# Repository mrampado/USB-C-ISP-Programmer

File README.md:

# USB-C-ISP-Programmer
ISP programmer for ATMEGA based Arduino boards with a USB C header, a more compact form, and easy to use design

Current status as of latest commit to master:
- Initial hardware complete, creating order to JLC
- More documentation to follow as hardware is received and brought up

### Bonus
A little bonus for those that reconize it

## License

This hardware is covered under the CERN-OHL-S-V2 open source hardware license. Details on this license can also be found [at this link](https://choosealicense.com/licenses/cern-ohl-s-2.0/). 

Software for this project is covered under GNU Public License v3.0. Details on this license can be found [at this link](https://choosealicense.com/licenses/gpl-3.0/)

As per the details in each of the licenses, replication is accepted under the provision that all commercial and individual replications must also follow the same license as in this project, and **remain fully open source**. 

While not required, please contact me before starting any commercialization efforts. At the current moment, I am unable to commercialize this project thus unable to sell finished boards. I am happy to (in a limited capacity) support anyone / business that wants to utilize my efforts with ALP to use as a basis for teaching anyone and everyone Arduino. 

It is my personal belief that this project shall remain open source for the entire community, with all schematics, gerber files, and code available to all. I have benefited greatly from the open source community and this project will hopefully help others learn and get started too!

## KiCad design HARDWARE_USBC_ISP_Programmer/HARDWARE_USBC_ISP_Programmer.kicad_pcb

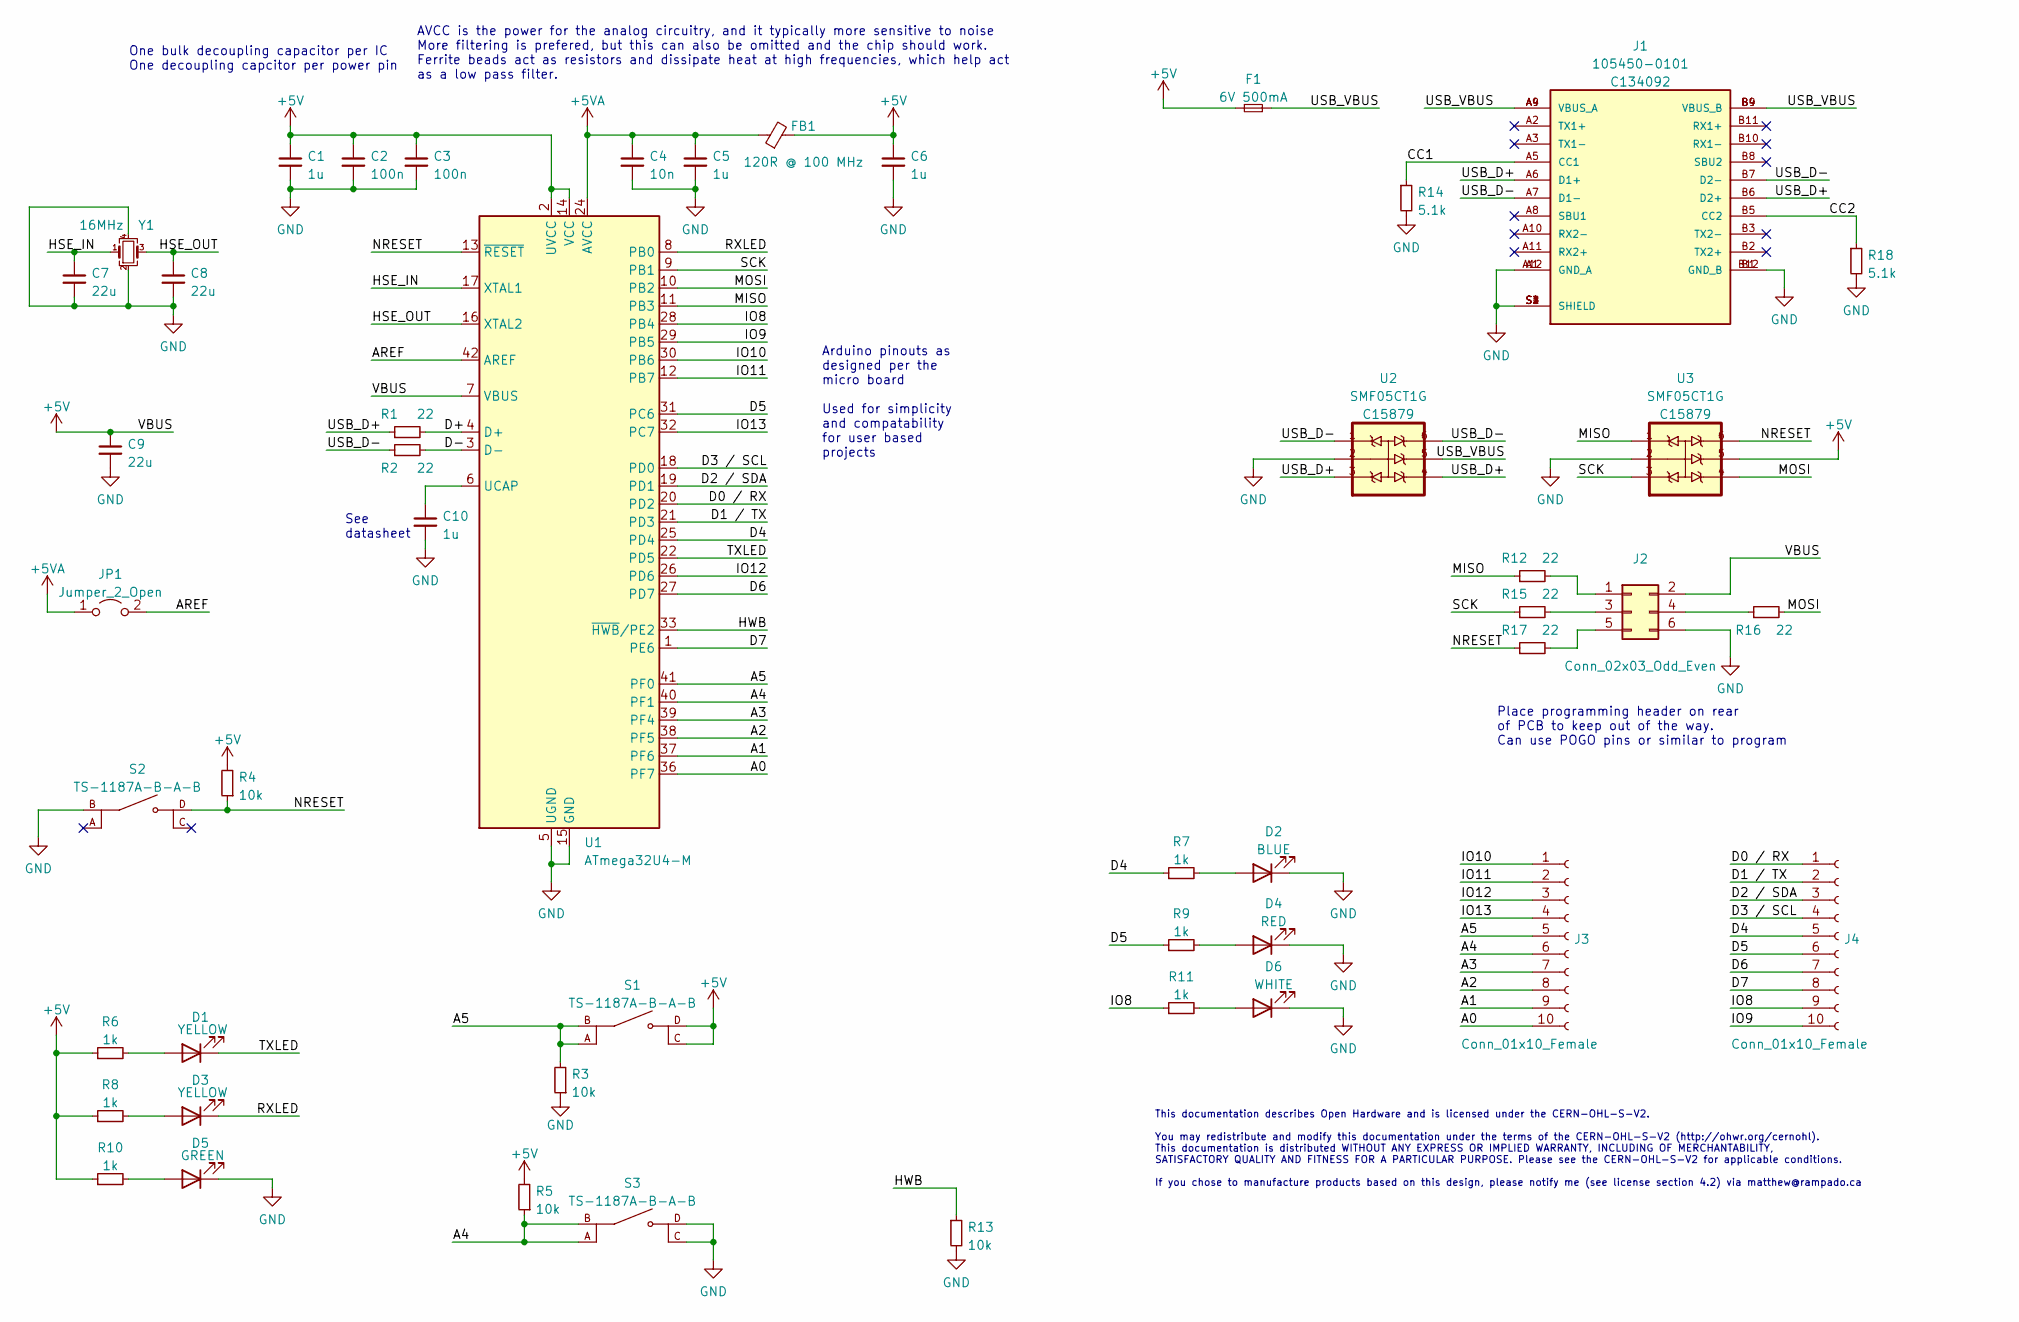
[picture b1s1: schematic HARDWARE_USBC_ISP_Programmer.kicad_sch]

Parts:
C1, C5, C6, C10: 1u; C_0603_1608Metric; JLCPCB Part # C15849
C2, C3: 100n; C_0603_1608Metric; JLCPCB Part # C14663
C4: 10n; C_0603_1608Metric; JLCPCB Part # C57112
C7, C8, C9: 22u; C_0603_1608Metric; JLCPCB Part # C59461
D1, D3: YELLOW; LED_0603_1608Metric; JLCPCB Part # C72038
D2: BLUE; LED_0603_1608Metric; JLCPCB Part # C72041
D4: RED; LED_0603_1608Metric; JLCPCB Part # C2286
D5: GREEN; LED_0603_1608Metric; JLCPCB Part # C72043
D6: WHITE; LED_0603_1608Metric; JLCPCB Part # C2290
F1: 6V 500mA; Fuse_0603_1608Metric_Pad1.05x0.95mm_HandSolder; JLCPCB Part # C135323
FB1: 120R @ 100 MHz; L_0805_2012Metric; JLCPCB Part # C1015
J1: 105450-0101; MOLEX_105450-0101; PARTREV A7; JLCPCB Part # C134092
J2: Conn_02x03_Odd_Even; PinHeader_2x03_P2.54mm_Vertical; JLCPCB Part # C65114
J3, J4: Conn_01x10_Female; PinSocket_1x10_P2.54mm_Vertical
JP1: Jumper_2_Open; SolderJumper-2_P1.3mm_Open_RoundedPad1.0x1.5mm; JLCPCB Part # N/A
R1, R2, R12, R15, R16, R17: 22; R_0603_1608Metric; JLCPCB Part # C23345
R3, R4, R5, R13: 10k; R_0603_1608Metric; JLCPCB Part # C25804
R6, R7, R8, R9, R10, R11: 1k; R_0603_1608Metric; JLCPCB Part # C21190
R14, R18: 5.1k; R_0603_1608Metric; JLCPCB Part # C23186
S1, S2, S3: TS-1187A-B-A-B; SW_TS-1187A-B-A-B; PARTREV A0; JLCPCB Part # C318884
U1: ATmega32U4-M; QFN-44-1EP_7x7mm_P0.5mm_EP5.2x5.2mm; JLCPCB Part # C112161
U2, U3: SMF05CT1G; SOT65P210X110-6N; JLCPCB Part # C15879
Y1: 16MHz; Crystal_SMD_3225-4Pin_3.2x2.5mm; JLCPCB Part # C112972

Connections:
+5V: C1.1, C2.1, C3.1, C6.1, C9.1, F1.1, FB1.2, J2.2, R4.2, R5.2, R6.1, R8.1, R10.1, S1.C, S1.D, U1.2 (UVCC), U1.7 (VBUS), U1.14 (VCC), U1.34 (VCC), U3.5
+5VA: C4.1, C5.1, FB1.1, JP1.1 (A), U1.24 (AVCC), U1.44 (AVCC)
/A0: J3.10, U1.36 (PF7)
/A1: J3.9, U1.37 (PF6)
/A2: J3.8, U1.38 (PF5)
/A3: J3.7, U1.39 (PF4)
/A4: J3.6, R5.1, S3.A, S3.B, U1.40 (PF1)
/A5: J3.5, R3.2, S1.A, S1.B, U1.41 (PF0)
/AREF: JP1.2 (B), U1.42 (AREF)
/CC1: J1.A5 (CC1), R14.1
/CC2: J1.B5 (CC2), R18.1
/D0 / RX: J4.1, U1.20 (PD2)
/D1 / TX: J4.2, U1.21 (PD3)
/D2 / SDA: J4.3, U1.19 (PD1)
/D3 / SCL: J4.4, U1.18 (PD0)
/D4: J4.5, R7.1, U1.25 (PD4)
/D5: J4.6, R9.1, U1.31 (PC6)
/D6: J4.7, U1.27 (PD7)
/D7: J4.8, U1.1 (PE6)
/D+: R1.2, U1.4 (D+)
/D-: R2.2, U1.3 (D-)
/HSE_IN: C7.1, U1.17 (XTAL1), Y1.1
/HSE_OUT: C8.1, U1.16 (XTAL2), Y1.3
/HWB: R13.1, U1.33 (~HWB/PE2)
/IO8: J4.9, R11.1, U1.28 (PB4)
/IO9: J4.10, U1.29 (PB5)
/IO10: J3.1, U1.30 (PB6)
/IO11: J3.2, U1.12 (PB7)
/IO12: J3.3, U1.26 (PD6)
/IO13: J3.4, U1.32 (PC7)
/MISO: R12.1, U1.11 (PB3), U3.1
/MOSI: R16.2, U1.10 (PB2), U3.4
/NRESET: R4.1, R17.1, S2.D, U1.13 (~RESET), U3.6
/RXLED: D3.1 (K), U1.8 (PB0)
/SCK: R15.1, U1.9 (PB1), U3.3
/TXLED: D1.1 (K), U1.22 (PD5)
/USB_D+: J1.A6 (D1+), J1.B6 (D2+), R1.1, U2.3, U2.4
/USB_D-: J1.A7 (D1-), J1.B7 (D2-), R2.1, U2.1, U2.6
/USB_VBUS: F1.2, J1.A4 (VBUS_A), J1.A9 (VBUS_A), J1.B4 (VBUS_B), J1.B9 (VBUS_B), U2.5
GND: C1.2, C2.2, C3.2, C4.2, C5.2, C6.2, C7.2, C8.2, C9.2, C10.2, D2.1 (K), D4.1 (K), D5.1 (K), D6.1 (K), J1.A1 (GND_A), J1.A12 (GND_A), J1.B1 (GND_B), J1.B12 (GND_B), J1.S1 (SHIELD), J1.S2 (SHIELD), J1.S3 (SHIELD), J1.S4 (SHIELD), J2.6, R3.1, R13.2, R14.2, R18.2, S2.B, S3.C, S3.D, U1.5 (UGND), U1.15 (GND), U1.23 (GND), U1.35 (GND), U1.43 (GND), U1.45 (GND), U2.2, U3.2, Y1.2, Y1.4
unnamed: C10.1, U1.6 (UCAP)
unnamed: D1.2 (A), R6.2
unnamed: D2.2 (A), R7.2
unnamed: D3.2 (A), R8.2
unnamed: D4.2 (A), R9.2
unnamed: D5.2 (A), R10.2
unnamed: D6.2 (A), R11.2
unnamed: J2.1, R12.2
unnamed: J2.3, R15.2
unnamed: J2.4, R16.1
unnamed: J2.5, R17.2

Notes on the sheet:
Place programming header on rear of PCB to keep out of the way. Can use POGO pins or similar to program
AVCC is the power for the analog circuitry, and it typically more sensitive to noise More filtering is prefered, but this can also be omitted and the chip should work. Ferrite beads act as resistors and dissipate heat at high frequencies, which help act as a low pass filter.
See datasheet
One bulk decoupling capacitor per IC One decoupling capcitor per power pin
This documentation describes Open Hardware and is licensed under the CERN-OHL-S-V2. You may redistribute and modify this documentation under the terms of the CERN-OHL-S-V2 (http://ohwr.org/cernohl). This documentation is distributed WITHOUT ANY EXPRESS OR IMPLIED WARRANTY, INCLUDING OF MERCHANTABIL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
Arduino pinouts as designed per the micro board Used for simplicity and compatability for user based projects

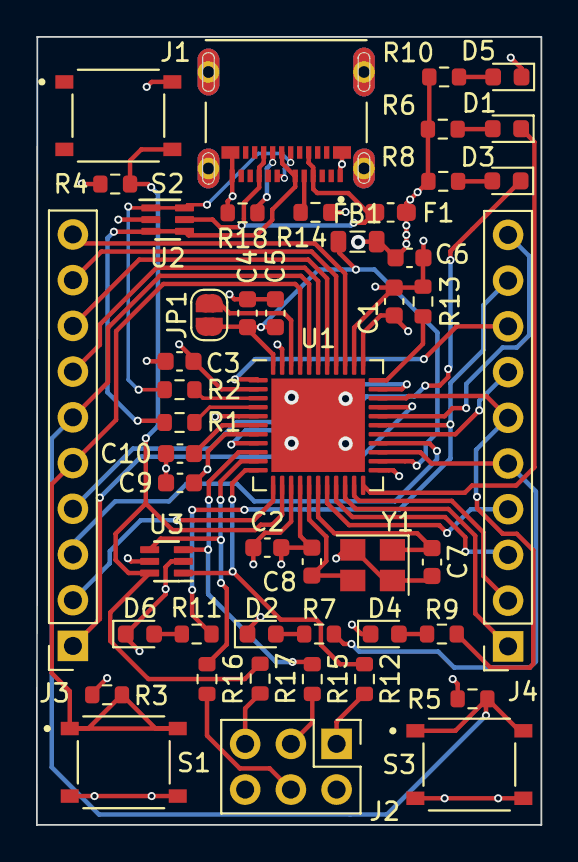
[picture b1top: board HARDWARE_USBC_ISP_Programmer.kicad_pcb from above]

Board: 4 copper layers, 28.0 x 43.8 mm, 48 parts (0 on the bottom side), 51 nets.

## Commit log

2022-08-26 KiCad project created
2022-08-26 Imported based schematic files
2022-08-26 Added headers to schematic, other minor changes
2022-08-26 Finalized footprints and schematic
2022-08-26 Initial PCB layout complete
2022-08-29 Routed USBC connector
    Will need to review, tricky connector to route with small vias, but knowing I am running with USB2 speeds I am not too concerned about impedance and perfect USB3.0 design.
    Need to make sure I am within JLC design limits (currently right on the edge)
2022-09-02 More routing completed
2022-09-02 V1 routing complete
2022-09-02 Created manufacturing files and prepare for review
2022-09-02 Updated readme with documentation
2022-09-02 Updated open source license
2022-09-10 Added PDF of schematic
2023-05-05 More changes

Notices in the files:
HARDWARE_USBC_ISP_Programmer/HARDWARE_USBC_ISP_Programmer.kicad_sch:
If you chose to manufacture products based on this design, please notify me (see license section 4.2) via matthew@rampado.ca
